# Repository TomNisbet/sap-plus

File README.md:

# SAP-Plus

A Simple As Possible (SAP) computer build using a modular PCB architecture.

Visit the [SAP-Plus documentation pages](https://tomnisbet.github.io/sap-plus/) for detailed design notes and schematics.

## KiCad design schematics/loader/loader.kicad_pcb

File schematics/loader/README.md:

# Arduino Loader and Debugger Module schematics

created with KiCad 8.0

## Changelog

### 1.2

* Change OLED power to 3.3V and add pullup resistors on SDA and SCL

### 1.1

* Fix U2 label to 7400 NAND, not 7408 AND
* Adjust OLED display footprint and position
* Add interconnect label to Microcode
* Change reset button from 6mm to 12mm size

### 1.0

* Initial version

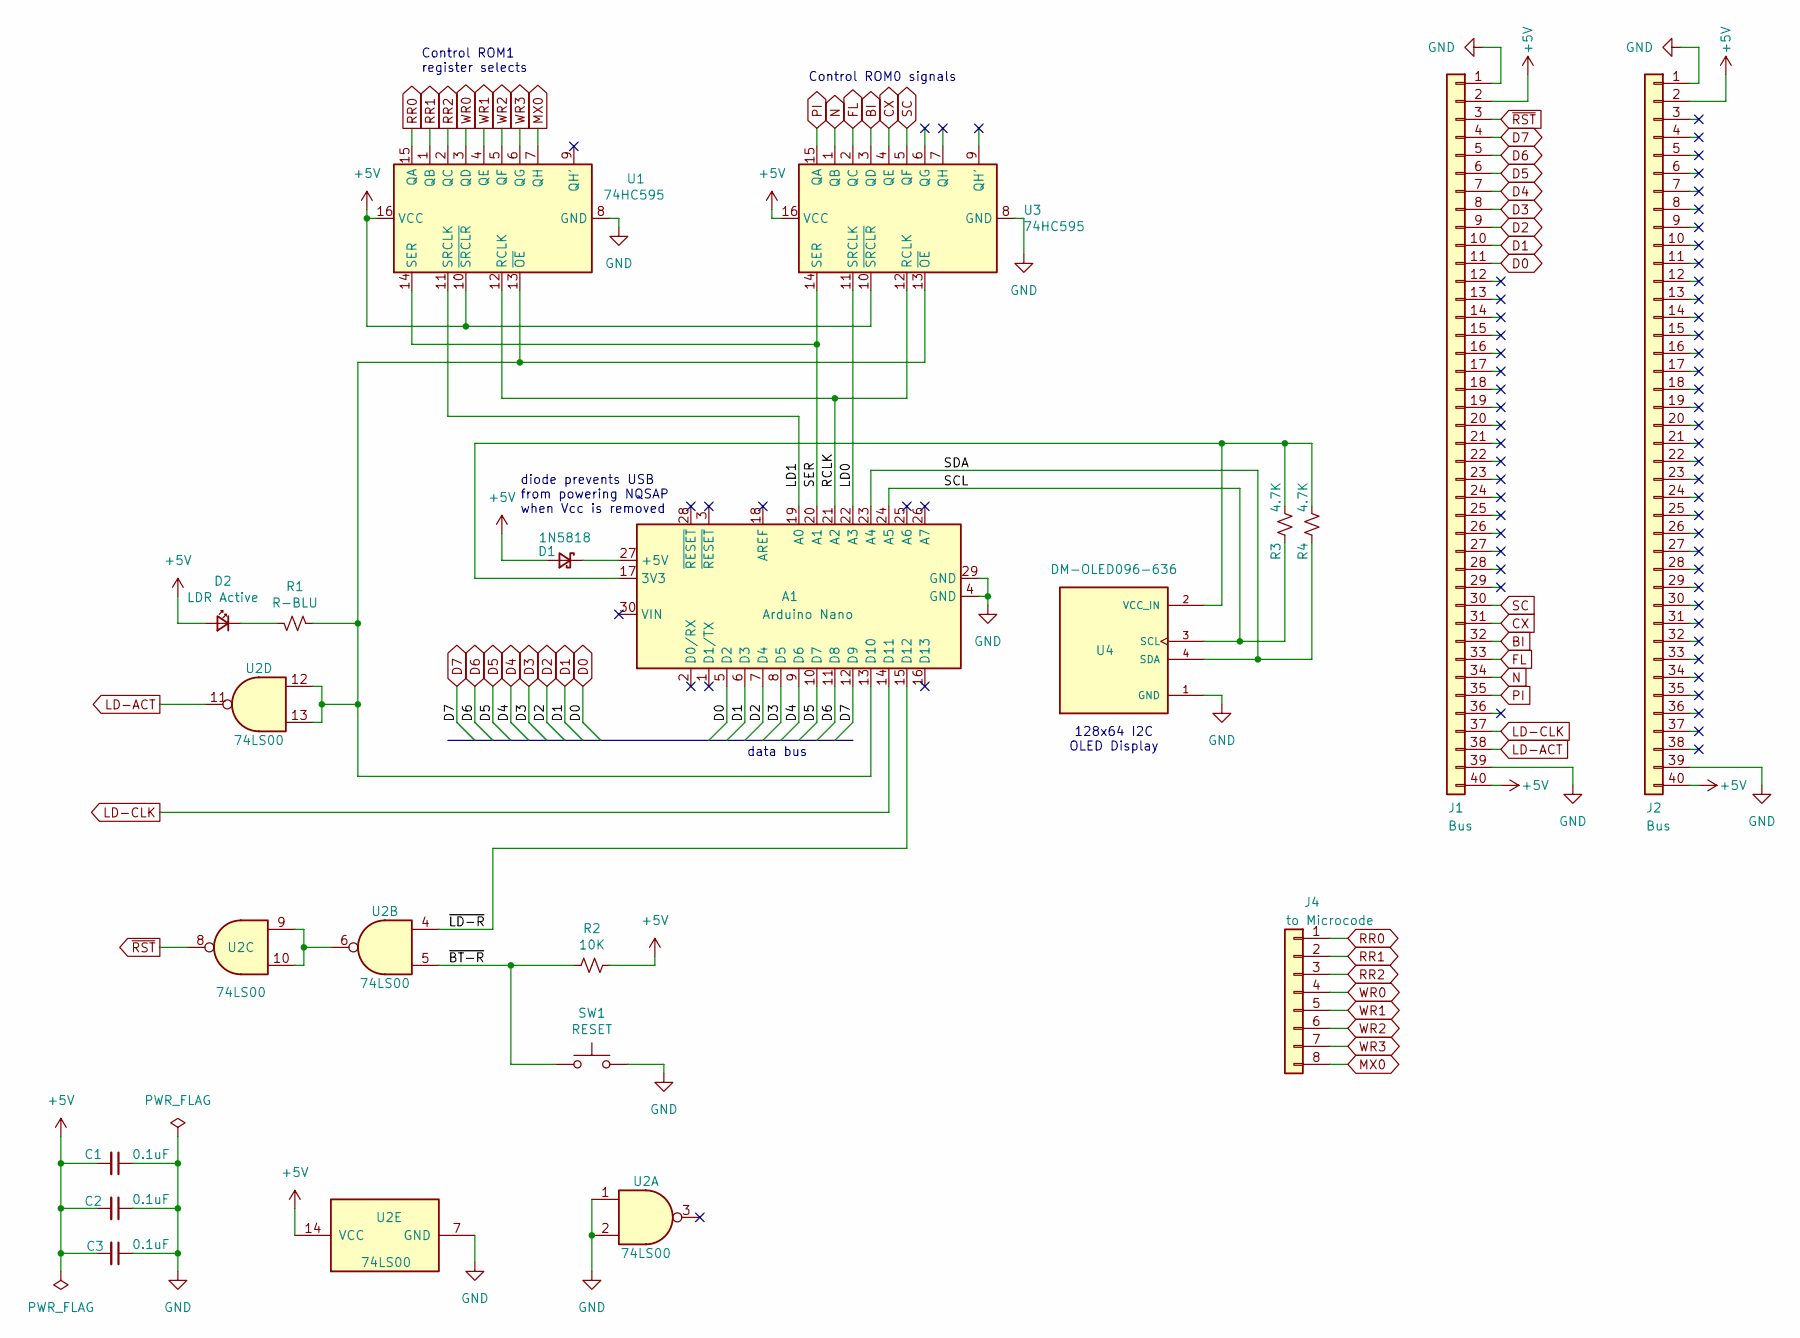
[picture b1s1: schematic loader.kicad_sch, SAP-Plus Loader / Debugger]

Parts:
A1: Arduino Nano; Arduino_Nano
C1, C2, C3: 0.1uF; C_Disc_D3.0mm_W1.6mm_P2.50mm
D1: 1N5818; D_DO-41_SOD81_P10.16mm_Horizontal
D2: LDR Active; LED_D5.0mm
J1, J2: Bus; PinHeader_1x40_P2.54mm_Vertical
J4: to Microcode; PinHeader_1x08_P2.54mm_Vertical
R1: R-BLU; R_Axial_DIN0207_L6.3mm_D2.5mm_P10.16mm_Horizontal
R2: 10K; R_Axial_DIN0207_L6.3mm_D2.5mm_P10.16mm_Horizontal
R3, R4: 4.7K; R_Axial_DIN0207_L6.3mm_D2.5mm_P10.16mm_Horizontal
SW1: RESET; SW_PUSH-12mm
U1, U3: 74HC595; DIP-16_W7.62mm
U2: 74LS00; DIP-14_W7.62mm
U4: DM-OLED096-636; MODULE_DM-OLED096-636-27; PARTREV 2018-09-10

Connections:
+5V: C1.2, C2.2, C3.2, D1.2 (A), D2.2 (A), J1.2, J1.40, J2.2, J2.40, R2.1, U1.10 (~SRCLR), U1.16 (VCC), U2.14 (VCC), U3.10 (~SRCLR), U3.16 (VCC)
/LD0: A1.22 (A3), U3.11 (SRCLK)
/LD1: A1.19 (A0), U1.11 (SRCLK)
/RCLK: A1.21 (A2), U1.12 (RCLK), U3.12 (RCLK)
/SCL: A1.24 (A5), R3.2, U4.3 (SCL)
/SDA: A1.23 (A4), R4.2, U4.4 (SDA)
/SER: A1.20 (A1), U1.14 (SER), U3.14 (SER)
/~BT-R: R2.2, SW1.2, U2.5
/~LD-R: A1.15 (D12), U2.4
BI: J1.32, U3.3 (QD)
CX: J1.31, U3.4 (QE)
D0: A1.5 (D2), J1.11
D1: A1.6 (D3), J1.10
D2: A1.7 (D4), J1.9
D3: A1.8 (D5), J1.8
D4: A1.9 (D6), J1.7
D5: A1.10 (D7), J1.6
D6: A1.11 (D8), J1.5
D7: A1.12 (D9), J1.4
FL: J1.33, U3.2 (QC)
GND: A1.4 (GND), A1.29 (GND), C1.1, C2.1, C3.1, J1.1, J1.39, J2.1, J2.39, SW1.1, U1.8 (GND), U2.1, U2.2, U2.7 (GND), U3.8 (GND), U4.1 (GND)
LD-ACT: J1.38, U2.11
LD-CLK: A1.14 (D11), J1.37
MX0: J4.8, U1.7 (QH)
N: J1.34, U3.1 (QB)
unnamed: A1.17 (3V3), R3.1, R4.1, U4.2 (VCC_IN)
unnamed: A1.27 (+5V), D1.1 (K)
unnamed: A1.13 (D10), R1.2, U1.13 (~OE), U2.12, U2.13, U3.13 (~OE)
unnamed: D2.1 (K), R1.1
unnamed: U2.6, U2.9, U2.10
PI: J1.35, U3.15 (QA)
RR0: J4.1, U1.15 (QA)
RR1: J4.2, U1.1 (QB)
RR2: J4.3, U1.2 (QC)
SC: J1.30, U3.5 (QF)
WR0: J4.4, U1.3 (QD)
WR1: J4.5, U1.4 (QE)
WR2: J4.6, U1.5 (QF)
WR3: J4.7, U1.6 (QG)
~RST: J1.3, U2.8

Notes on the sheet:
diode prevents USB from powering NQSAP when Vcc is removed
Control ROM1 register selects
Control ROM0 signals
128x64 I2C OLED Display
data bus

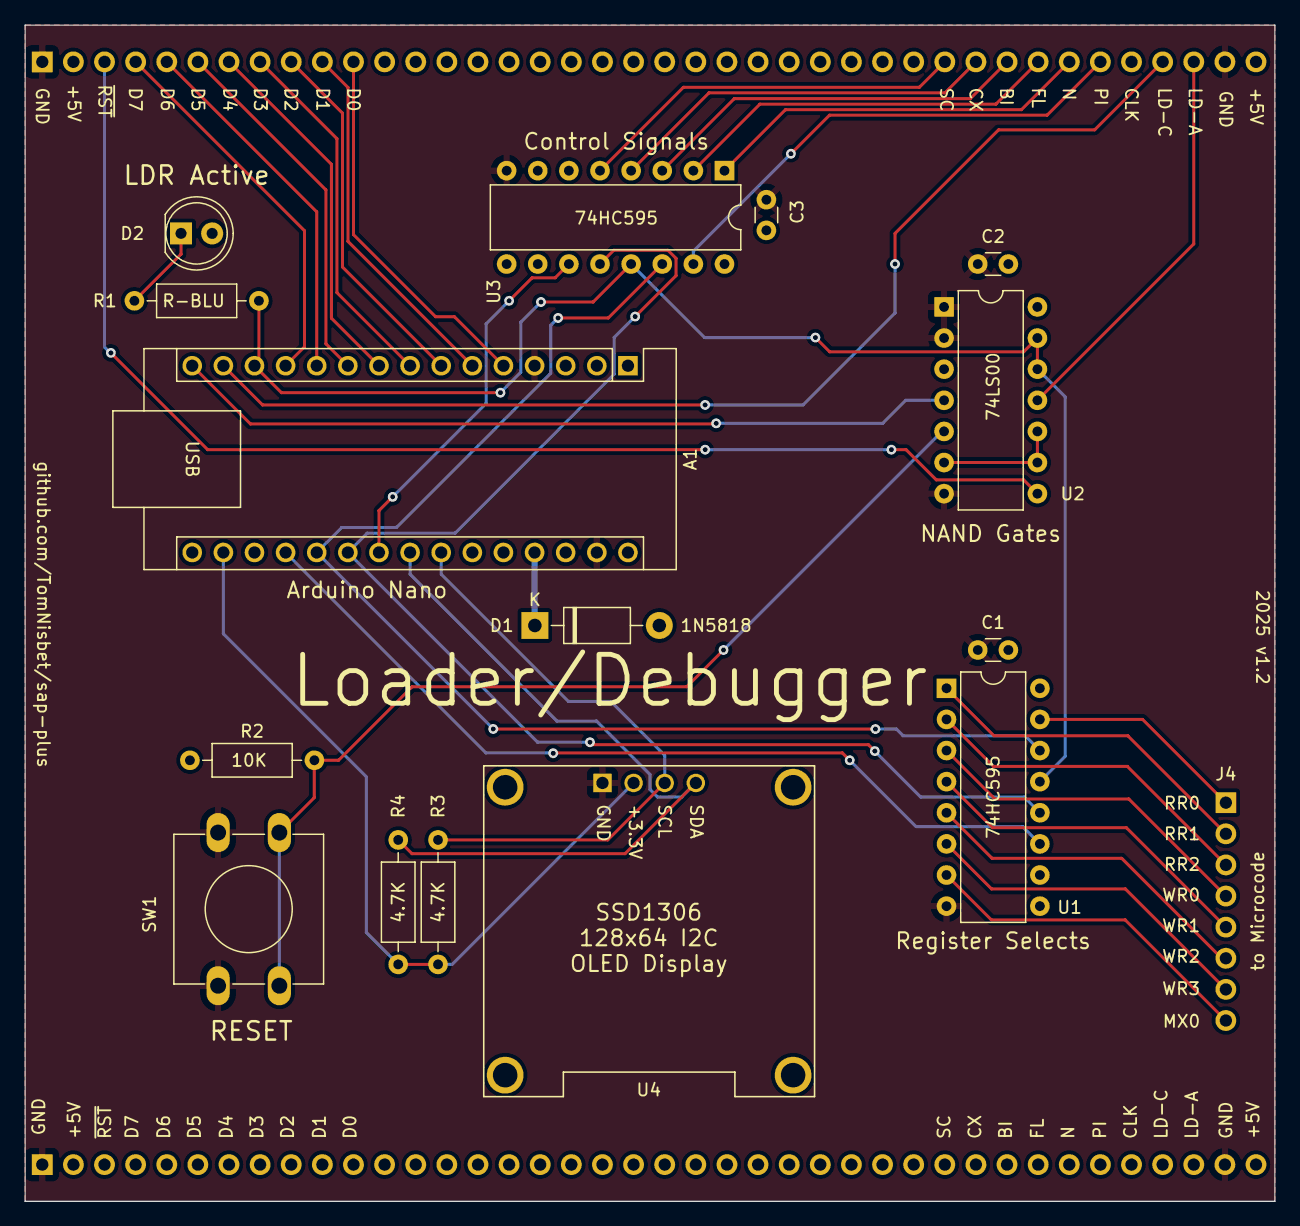
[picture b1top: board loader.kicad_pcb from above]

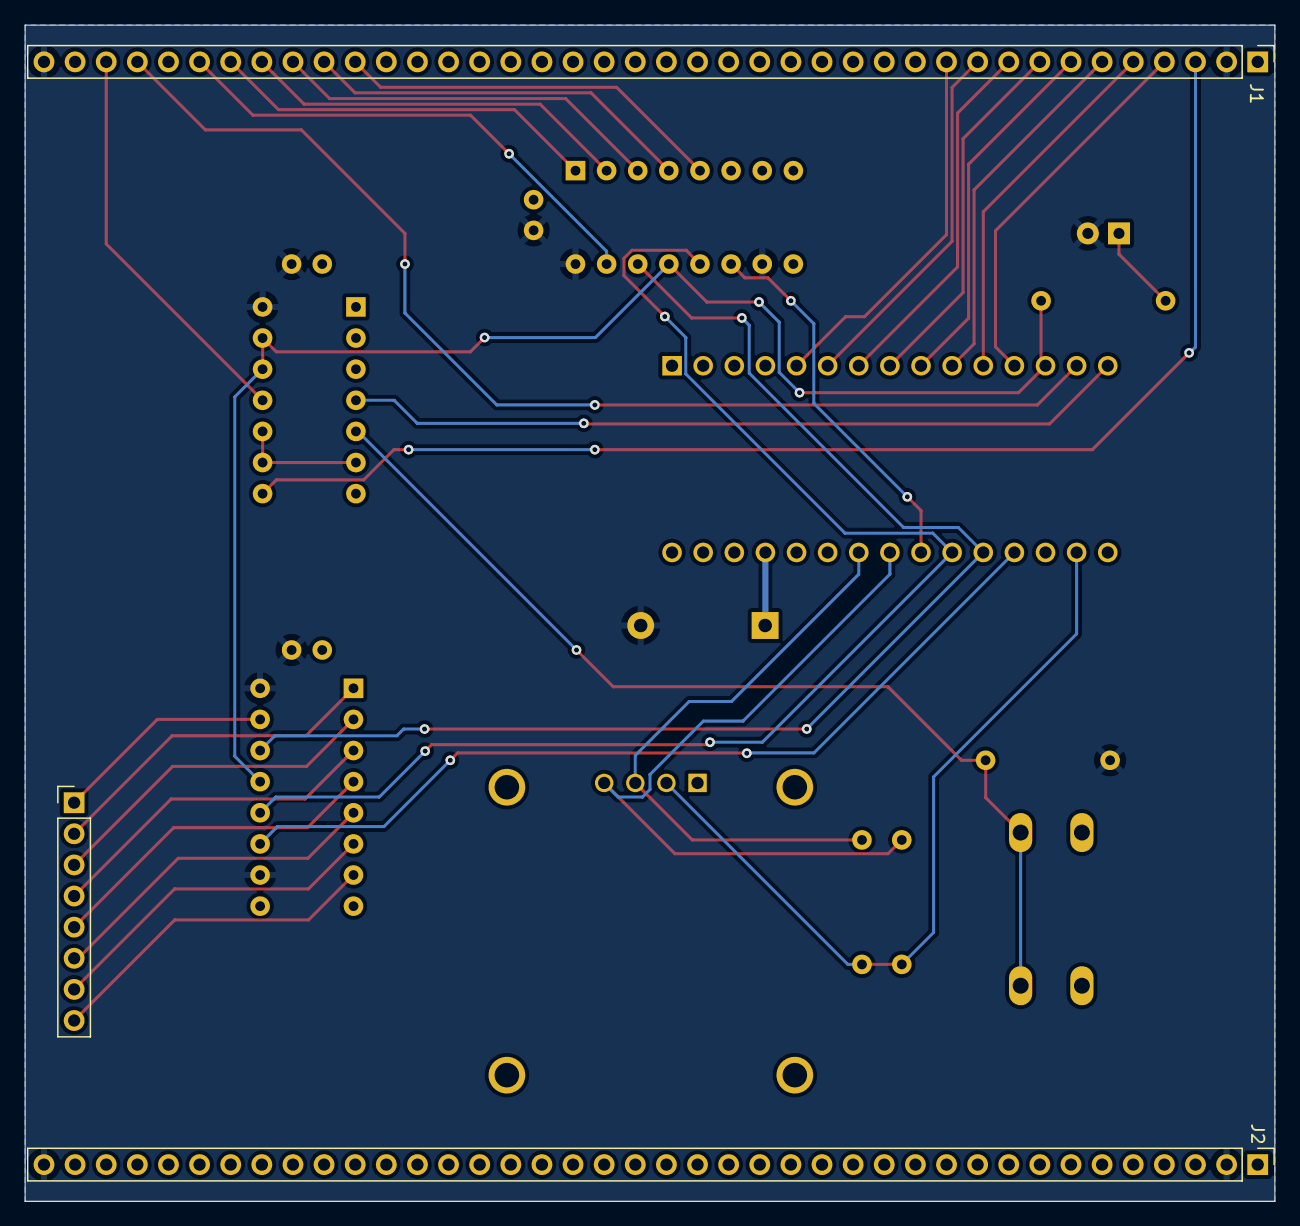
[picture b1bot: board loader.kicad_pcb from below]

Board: 2 copper layers, 102.0 x 96.0 mm, 18 parts (3 on the bottom side), 40 nets.

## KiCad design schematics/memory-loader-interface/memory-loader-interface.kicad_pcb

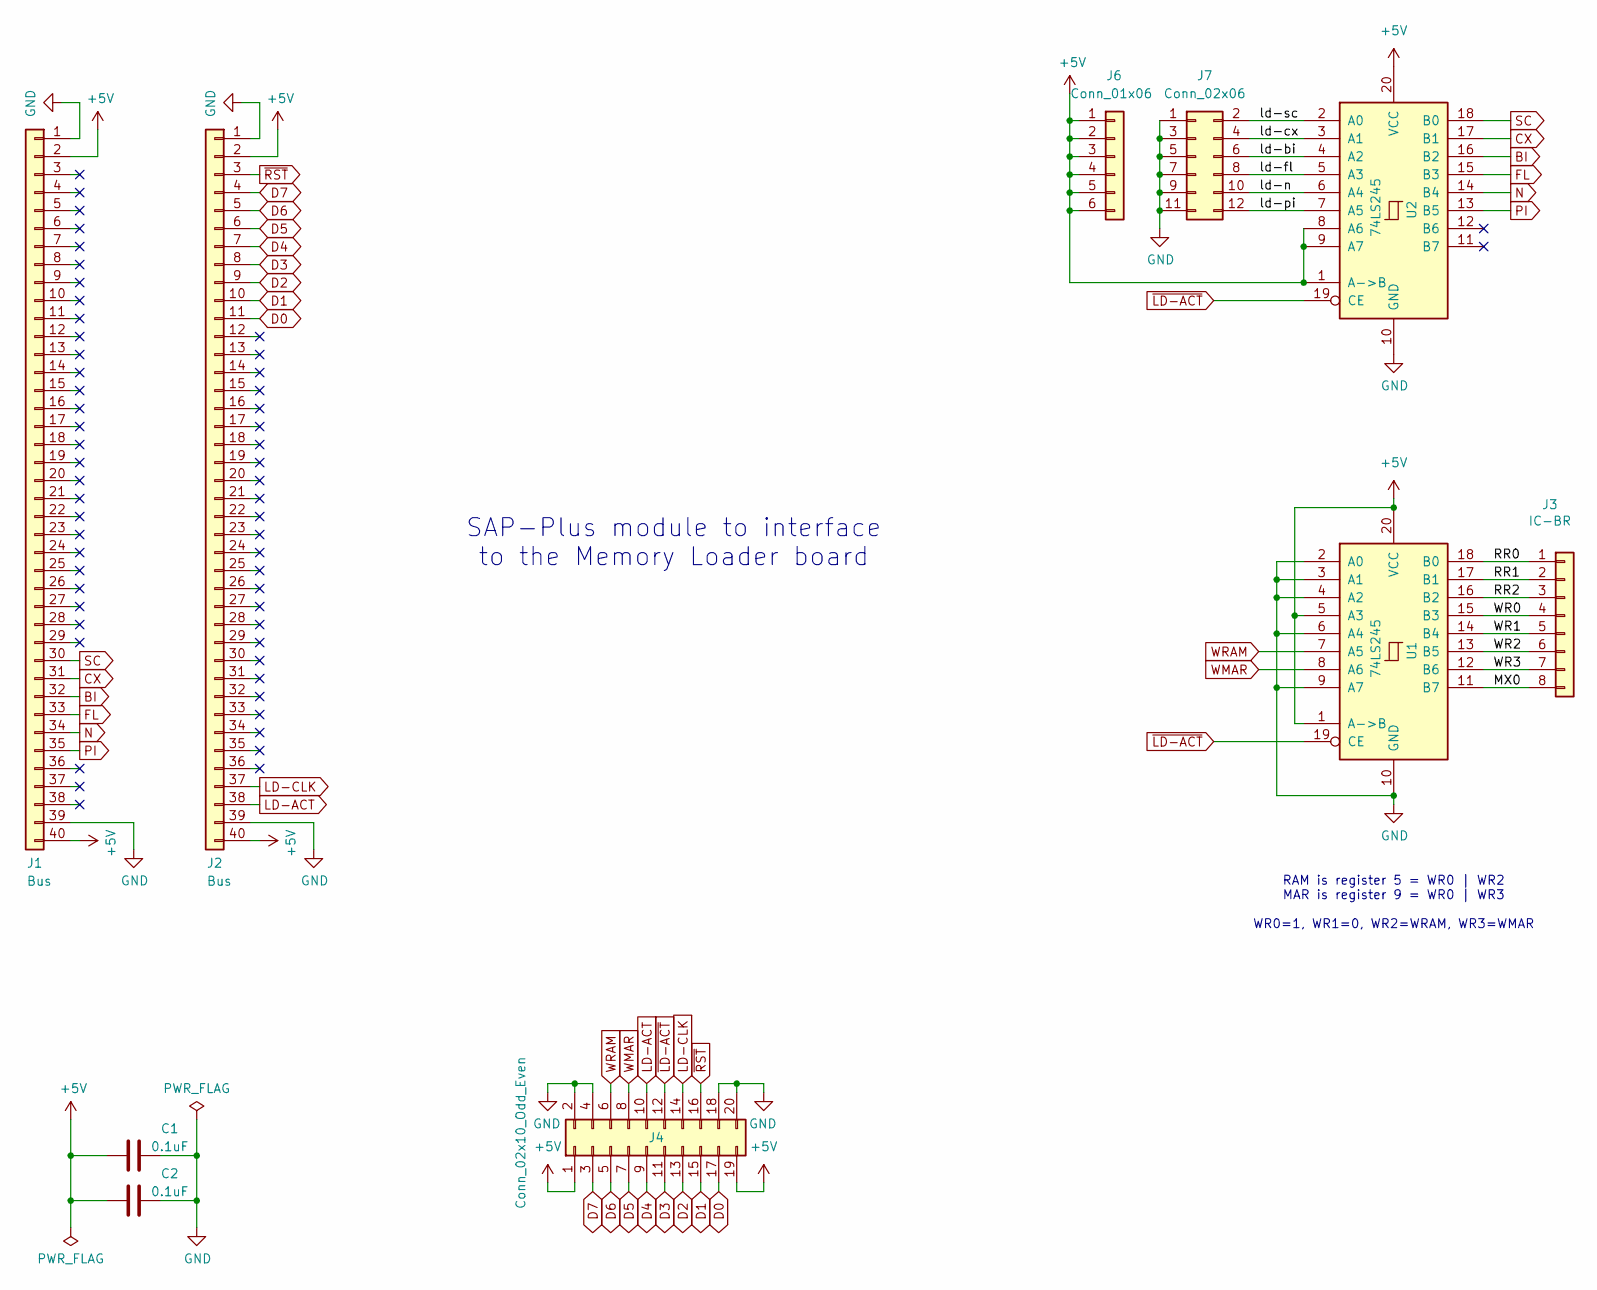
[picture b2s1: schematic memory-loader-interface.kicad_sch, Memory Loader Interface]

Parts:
C1, C2: 0.1uF; C_Disc_D3.0mm_W1.6mm_P2.50mm
J1, J2: Bus; PinHeader_1x40_P2.54mm_Vertical
J3: IC-BR; PinHeader_1x08_P2.54mm_Vertical
J4: Conn_02x10_Odd_Even; PinHeader_2x10_P2.54mm_Vertical
J6: Conn_01x06; PinHeader_1x06_P2.54mm_Vertical
J7: Conn_02x06; PinHeader_2x06_P2.54mm_Vertical
U1, U2: 74LS245; DIP-20_W7.62mm

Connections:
+5V: C1.2, C2.2, J1.2, J1.40, J2.2, J2.40, J4.1, J4.19, J6.1, J6.2, J6.3, J6.4, J6.5, J6.6, U1.1 (A->B), U1.5 (A3), U1.20 (VCC), U2.1 (A->B), U2.8 (A6), U2.9 (A7), U2.20 (VCC)
/MX0: J3.8, U1.11 (B7)
/RR0: J3.1, U1.18 (B0)
/RR1: J3.2, U1.17 (B1)
/RR2: J3.3, U1.16 (B2)
/WR0: J3.4, U1.15 (B3)
/WR1: J3.5, U1.14 (B4)
/WR2: J3.6, U1.13 (B5)
/WR3: J3.7, U1.12 (B6)
/ld-bi: J7.6, U2.4 (A2)
/ld-cx: J7.4, U2.3 (A1)
/ld-fl: J7.8, U2.5 (A3)
/ld-n: J7.10, U2.6 (A4)
/ld-pi: J7.12, U2.7 (A5)
/ld-sc: J7.2, U2.2 (A0)
BI: J1.32, U2.16 (B2)
CX: J1.31, U2.17 (B1)
D0: J2.11, J4.17
D1: J2.10, J4.15
D2: J2.9, J4.13
D3: J2.8, J4.11
D4: J2.7, J4.9
D5: J2.6, J4.7
D6: J2.5, J4.5
D7: J2.4, J4.3
FL: J1.33, U2.15 (B3)
GND: C1.1, C2.1, J1.1, J1.39, J2.1, J2.39, J4.2, J4.4, J4.18, J4.20, J7.1, J7.3, J7.5, J7.7, J7.9, J7.11, U1.2 (A0), U1.3 (A1), U1.4 (A2), U1.6 (A4), U1.9 (A7), U1.10 (GND), U2.10 (GND)
LD-ACT: J2.38, J4.10
LD-CLK: J2.37, J4.14
N: J1.34, U2.14 (B4)
PI: J1.35, U2.13 (B5)
SC: J1.30, U2.18 (B0)
WMAR: J4.8, U1.8 (A6)
WRAM: J4.6, U1.7 (A5)
~LD-ACT: J4.12, U1.19 (CE), U2.19 (CE)
~RST: J2.3, J4.16

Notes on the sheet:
RAM is register 5 = WR0 | WR2 MAR is register 9 = WR0 | WR3 WR0=1, WR1=0, WR2=WRAM, WR3=WMAR
SAP-Plus module to interface to the Memory Loader board

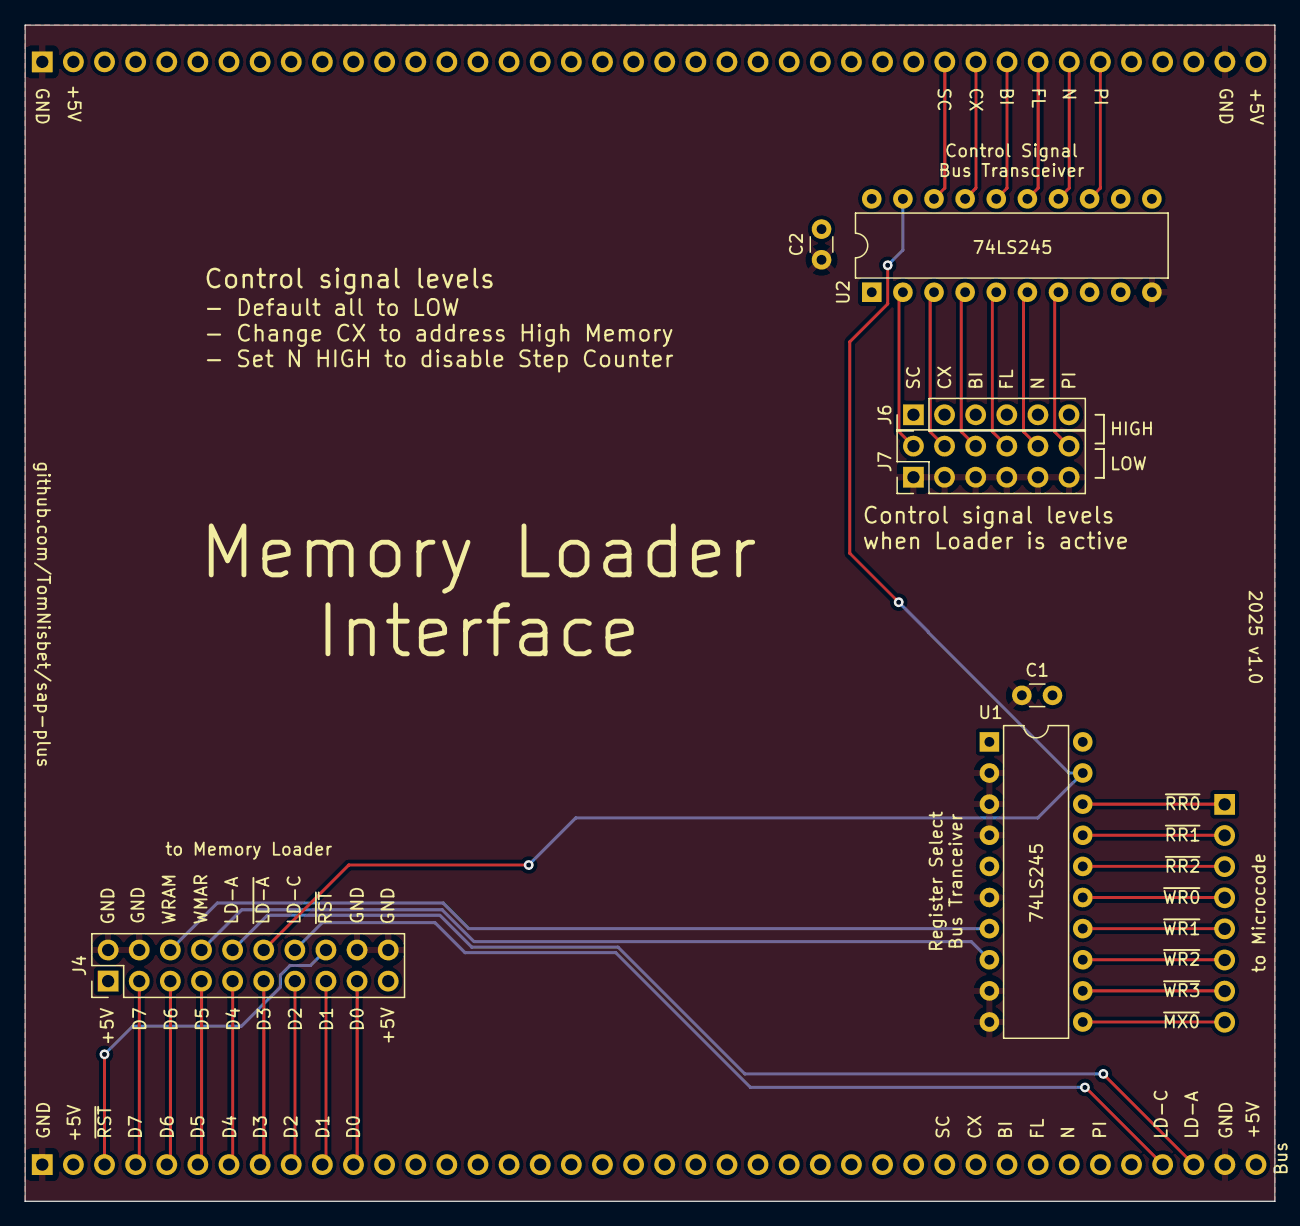
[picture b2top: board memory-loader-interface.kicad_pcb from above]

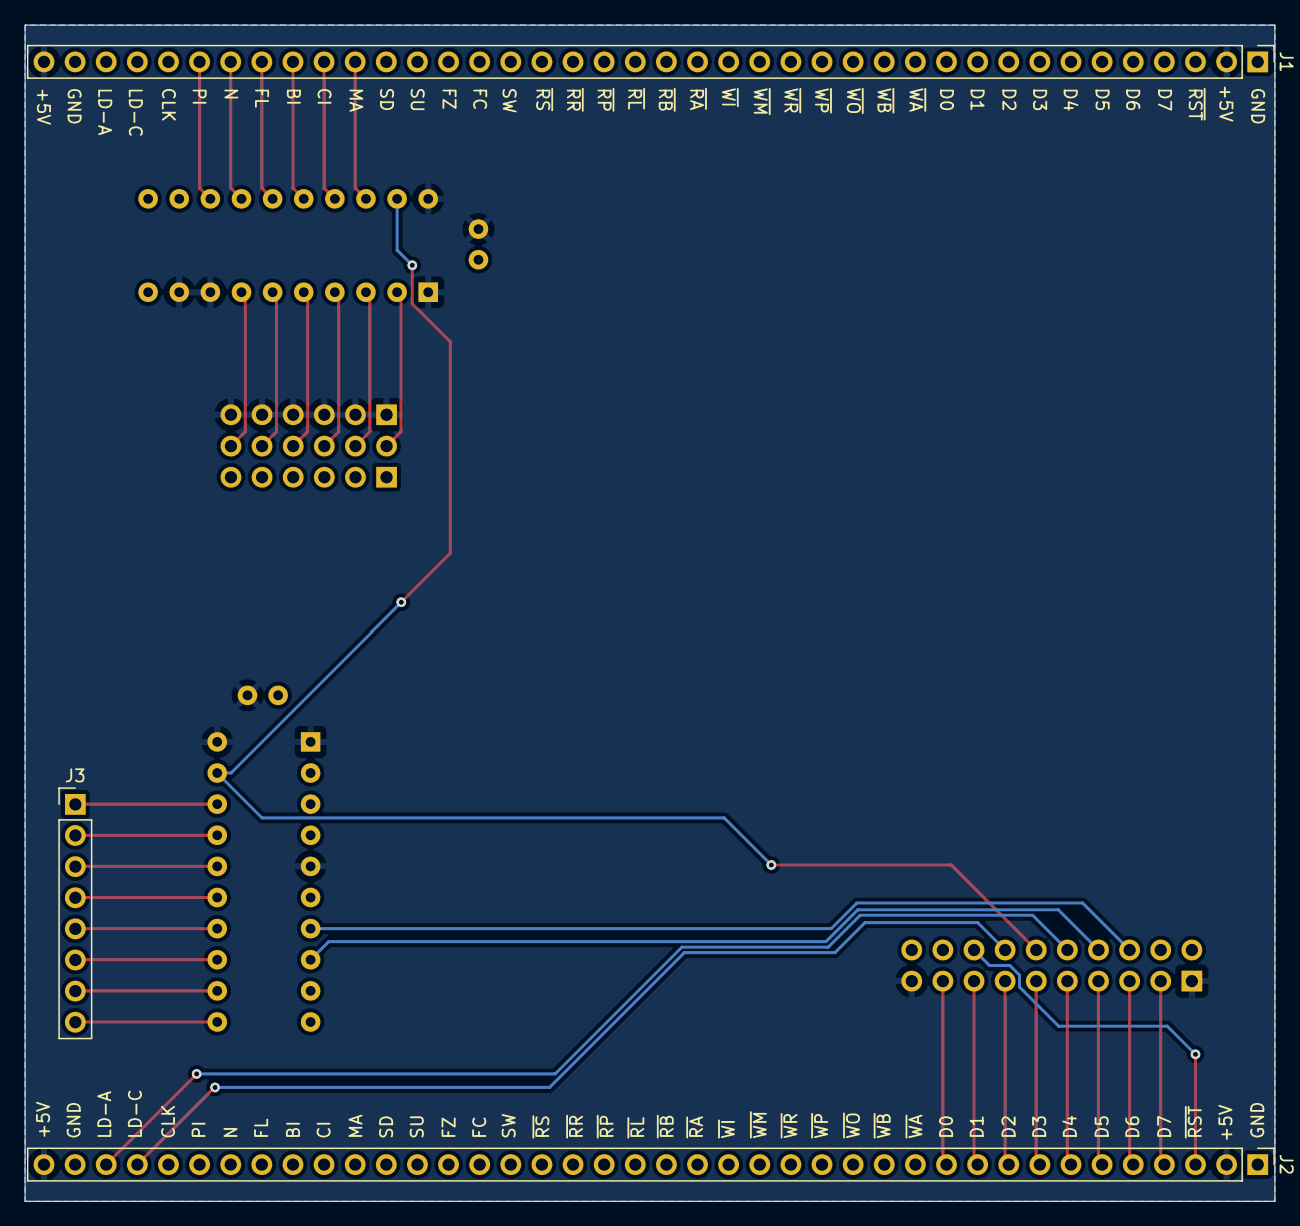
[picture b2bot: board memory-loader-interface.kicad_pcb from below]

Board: 2 copper layers, 102.0 x 96.0 mm, 10 parts (3 on the bottom side), 36 nets.

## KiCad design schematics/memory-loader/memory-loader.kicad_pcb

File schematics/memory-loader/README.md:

# Manual Memory Loader Module schematics

created with KiCad 8.0

## Changelog

### 3.0

* Add RAM READ/WRITE switch to allow read back of RAM values by holding the flip-flop in reset and writing only to the MAR
* RST signal no longer resets the state flip-flow
* Clean up silkscreen labels with new text and positioning

### 2.0

* Switch clock phase on state flip-flop and LAR counter - state now uses inverted CLK to change on falling edge and LAR uses CLK
* LAR now increments in WRAM state instead of WMAR state - this means that the LAR LEDs will show the current MAR address while the user is setting the switches for the RAM value
* New footprint for rocker switches SW1..SW8 with larger holes
* Remove DOWN and HOLD switches and resistors
* Fix R9 and R10 labels swapped on schematic
* Add silkscreen vlues for RN1 and RN2
* RST signal now resets the state flip-flip
* ACTIVE and UP switches changed to SPDT in schematic to reflect usage on PCB
* UP switch now uses pull-up instead of pull-down resistor
* Add power input connector

### 1.0

* Initial version

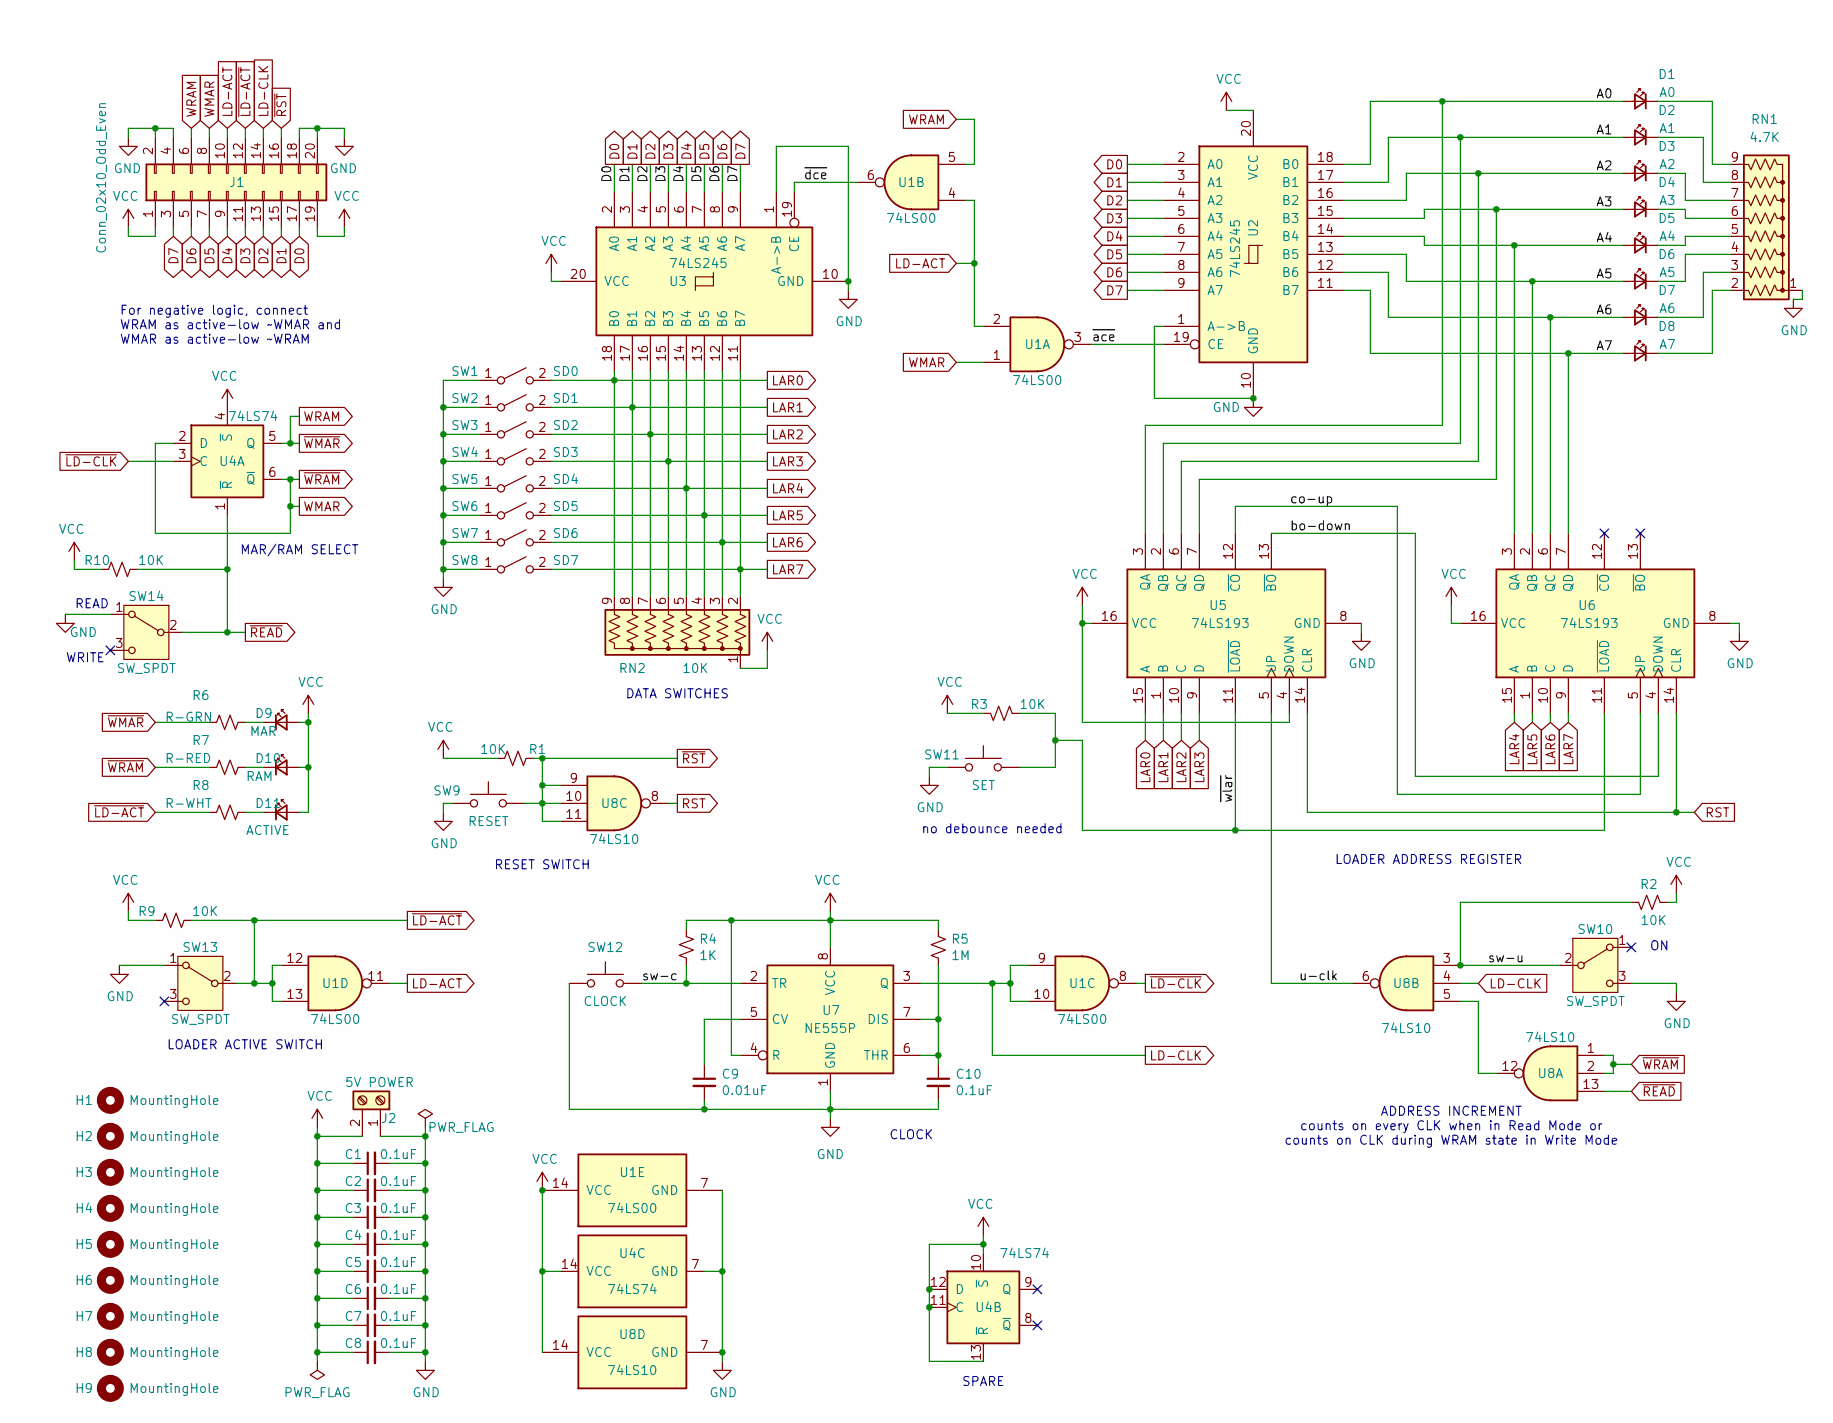
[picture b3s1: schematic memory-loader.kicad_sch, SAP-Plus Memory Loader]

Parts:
C1, C2, C3, C4, C5, C6, C7, C8, C10: 0.1uF; C_Disc_D3.0mm_W1.6mm_P2.50mm
C9: 0.01uF; C_Disc_D3.0mm_W1.6mm_P2.50mm
D1: A0; LED_D3.0mm
D2: A1; LED_D3.0mm
D3: A2; LED_D3.0mm
D4: A3; LED_D3.0mm
D5: A4; LED_D3.0mm
D6: A5; LED_D3.0mm
D7: A6; LED_D3.0mm
D8: A7; LED_D3.0mm
D9: MAR; LED_D3.0mm
D10: RAM; LED_D3.0mm
D11: ACTIVE; LED_D3.0mm
H1, H2, H3, H4, H5, H6, H7, H8, H9: MountingHole; MountingHole_3.2mm_M3
J1: Conn_02x10_Odd_Even; PinHeader_2x10_P2.54mm_Vertical
J2: 5V POWER; TerminalBlock_RND_205-00012_1x02_P5.00mm_Horizontal
R1, R2, R3, R9, R10: 10K; R_Axial_DIN0207_L6.3mm_D2.5mm_P10.16mm_Horizontal
R4: 1K; R_Axial_DIN0207_L6.3mm_D2.5mm_P10.16mm_Horizontal
R5: 1M; R_Axial_DIN0207_L6.3mm_D2.5mm_P10.16mm_Horizontal
R6: R-GRN; R_Axial_DIN0207_L6.3mm_D2.5mm_P10.16mm_Horizontal
R7: R-RED; R_Axial_DIN0207_L6.3mm_D2.5mm_P10.16mm_Horizontal
R8: R-WHT; R_Axial_DIN0207_L6.3mm_D2.5mm_P10.16mm_Horizontal
RN1: 4.7K; R_Array_SIP9
RN2: 10K; R_Array_SIP9
SW1: SD0; RockerSwitch CIT RA-14xxxxC
SW2: SD1; RockerSwitch CIT RA-14xxxxC
SW3: SD2; RockerSwitch CIT RA-14xxxxC
SW4: SD3; RockerSwitch CIT RA-14xxxxC
SW5: SD4; RockerSwitch CIT RA-14xxxxC
SW6: SD5; RockerSwitch CIT RA-14xxxxC
SW7: SD6; RockerSwitch CIT RA-14xxxxC
SW8: SD7; RockerSwitch CIT RA-14xxxxC
SW9: RESET; SW_PUSH-12mm_Wuerth-430476085716
SW10, SW13, SW14: SW_SPDT; SW_EG1218
SW11: SET; SW_PUSH-12mm_Wuerth-430476085716
SW12: CLOCK; SW_PUSH-12mm
U1: 74LS00; DIP-14_W7.62mm
U2, U3: 74LS245; DIP-20_W7.62mm
U4: 74LS74; DIP-14_W7.62mm
U5, U6: 74LS193; DIP-16_W7.62mm
U7: NE555P; DIP-8_W7.62mm
U8: 74LS10; DIP-14_W7.62mm

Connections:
/A0: D1.2 (A), U2.18 (B0), U5.3 (QA)
/A1: D2.2 (A), U2.17 (B1), U5.2 (QB)
/A2: D3.2 (A), U2.16 (B2), U5.6 (QC)
/A3: D4.2 (A), U2.15 (B3), U5.7 (QD)
/A4: D5.2 (A), U2.14 (B4), U6.3 (QA)
/A5: D6.2 (A), U2.13 (B5), U6.2 (QB)
/A6: D7.2 (A), U2.12 (B6), U6.6 (QC)
/A7: D8.2 (A), U2.11 (B7), U6.7 (QD)
/bo-down: U5.13 (~BO), U6.4 (DOWN)
/co-up: U5.12 (~CO), U6.5 (UP)
/sw-c: R4.2, SW12.2, U7.2 (TR)
/sw-u: R2.1, SW10.2 (B), U8.3
/u-clk: U5.5 (UP), U8.6
/~ace: U1.3, U2.19 (CE)
/~dce: U1.6, U3.19 (CE)
/~wlar: R3.2, SW11.2, U5.11 (~LOAD), U6.11 (~LOAD)
D0: J1.17, U2.2 (A0), U3.2 (A0)
D1: J1.15, U2.3 (A1), U3.3 (A1)
D2: J1.13, U2.4 (A2), U3.4 (A2)
D3: J1.11, U2.5 (A3), U3.5 (A3)
D4: J1.9, U2.6 (A4), U3.6 (A4)
D5: J1.7, U2.7 (A5), U3.7 (A5)
D6: J1.5, U2.8 (A6), U3.8 (A6)
D7: J1.3, U2.9 (A7), U3.9 (A7)
GND: C1.2, C2.2, C3.2, C4.2, C5.2, C6.2, C7.2, C8.2, C9.2, C10.2, J1.2, J1.4, J1.18, J1.20, J2.1, RN1.1 (common), SW1.1 (A), SW2.1 (A), SW3.1 (A), SW4.1 (A), SW5.1 (A), SW6.1 (A), SW7.1 (A), SW8.1 (A), SW9.1, SW10.3 (C), SW11.1, SW12.1, SW13.1 (A), SW14.1 (A), U1.7 (GND), U2.1 (A->B), U2.10 (GND), U3.1 (A->B), U3.10 (GND), U4.7 (GND), U5.8 (GND), U6.8 (GND), U7.1 (GND), U8.7 (GND)
LAR0: RN2.9 (R8), SW1.2 (B), U3.18 (B0), U5.15 (A)
LAR1: RN2.8 (R7), SW2.2 (B), U3.17 (B1), U5.1 (B)
LAR2: RN2.7 (R6), SW3.2 (B), U3.16 (B2), U5.10 (C)
LAR3: RN2.6 (R5), SW4.2 (B), U3.15 (B3), U5.9 (D)
LAR4: RN2.5 (R4), SW5.2 (B), U3.14 (B4), U6.15 (A)
LAR5: RN2.4 (R3), SW6.2 (B), U3.13 (B5), U6.1 (B)
LAR6: RN2.3 (R2), SW7.2 (B), U3.12 (B6), U6.10 (C)
LAR7: RN2.2 (R1), SW8.2 (B), U3.11 (B7), U6.9 (D)
LD-ACT: J1.10, U1.2, U1.4, U1.11
LD-CLK: J1.14, U1.9, U1.10, U7.3 (Q), U8.4
unnamed: D1.1 (K), RN1.9 (R8)
unnamed: D2.1 (K), RN1.8 (R7)
unnamed: D3.1 (K), RN1.7 (R6)
unnamed: D4.1 (K), RN1.6 (R5)
unnamed: D5.1 (K), RN1.5 (R4)
unnamed: D6.1 (K), RN1.4 (R3)
unnamed: D7.1 (K), RN1.3 (R2)
unnamed: D8.1 (K), RN1.2 (R1)
unnamed: D9.1 (K), R6.1
unnamed: D10.1 (K), R7.1
unnamed: D11.1 (K), R8.1
unnamed: C9.1, U7.5 (CV)
unnamed: C10.1, R5.2, U7.6 (THR), U7.7 (DIS)
unnamed: U8.5, U8.12
RST: U5.14 (CLR), U6.14 (CLR), U8.8
VCC: C1.1, C2.1, C3.1, C4.1, C5.1, C6.1, C7.1, C8.1, D9.2 (A), D10.2 (A), D11.2 (A), J1.1, J1.19, J2.2, R1.2, R2.2, R3.1, R4.1, R5.1, R9.2, R10.2, RN2.1 (common), U1.14 (VCC), U2.20 (VCC), U3.20 (VCC), U4.4 (~S), U4.10 (~S), U4.11 (C), U4.12 (D), U4.13 (~R), U4.14 (VCC), U5.4 (DOWN), U5.16 (VCC), U6.16 (VCC), U7.4 (R), U7.8 (VCC), U8.14 (VCC)
WMAR: J1.8, R7.2, U1.1, U4.2 (D), U4.6 (~Q), U8.1, U8.2
WRAM: J1.6, R6.2, U1.5, U4.5 (Q)
~LD-ACT: J1.12, R8.2, R9.1, SW13.2 (B), U1.12, U1.13
~LD-CLK: U1.8, U4.3 (C)
~READ: R10.1, SW14.2 (B), U4.1 (~R), U8.13
~RST: J1.16, R1.1, SW9.2, U8.9, U8.10, U8.11

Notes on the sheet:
LOADER ADDRESS REGISTER
WRITE
READ
ADDRESS INCREMENT counts on every CLK when in Read Mode or counts on CLK during WRAM state in Write Mode
SPARE
LOADER ACTIVE SWITCH
RESET SWITCH
MAR/RAM SELECT
For negative logic, connect WRAM as active-low ~WMAR and WMAR as active-low ~WRAM
DATA SWITCHES
no debounce needed
CLOCK

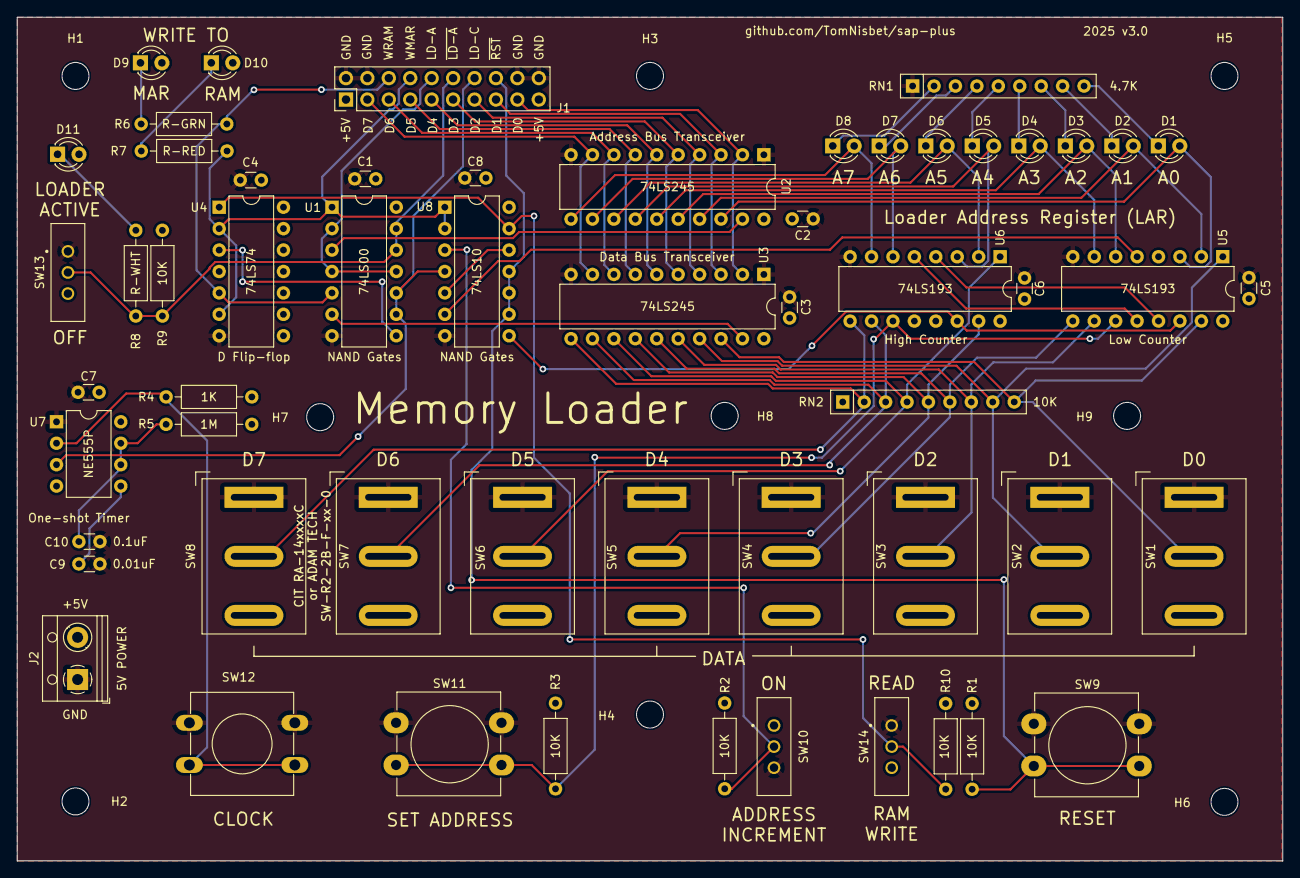
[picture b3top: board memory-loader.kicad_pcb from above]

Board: 2 copper layers, 150.0 x 100.0 mm, 66 parts (0 on the bottom side), 57 nets.
